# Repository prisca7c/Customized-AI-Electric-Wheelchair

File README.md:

# Customized-AI-Electric-Wheelchair

>PRISCA CHIEN | U0741Q95Y02
>
>July 27 2025
---

Manual wheelchair turned electric! This wheelchair uses electronic components such as modules and a PCB to make this wheelchair much for user interactive (and helps make life easier when you can't walk). 
I built this custom wheelchair because electric wheelchairs cost too much. Also it would be a great gift to my grandpa as he has Parkinson's disease. It has most of the functions on a regular wheelchair (motors, sound, speed, SOS, etc) AND I will be using AI as a healthcare tool in this project. 

---

## Full 3D Model of Wheelchair with Electronics (will not have those cuffs IRL 💀)

## PCB Schematic

## PCB Wiring Diagram (strapping 24V fan on just in case it does overheat), back copper pours for 24V, front copper pours for 12V I can't fit the wires if they're too large

## 3D View of PCB

---

# Bill of Materials (BOM)

| Reference | Qty | Description | Footprint | Purchase Link | Status |
|-----------|-----|-------------|-----------|---------------|---------|
| C1,C2,C3,C4,C6,C20,C23,C25 | 8 | Polarized Capacitor | CP_Radial_D5.0mm_P2.50mm | [AliExpress](https://www.aliexpress.com/item/1005002524973878.html) | |
| C5,C7,C8,C9,C10,C11,C12,C13,C14,C15,C16,C17,C18,C19,C22,C24 | 16 | Ceramic Capacitor | C_0603_1608Metric | [AliExpress](https://www.aliexpress.com/item/33000528620.html) | |
| C21 | 1 | Ceramic Capacitor (45°) | C_0603_1608Metric | [AliExpress](https://www.aliexpress.com/item/33000528620.html) | |
| D1 | 1 | TVS Diode | D_SMA | [AliExpress](https://www.aliexpress.com/item/1005002276080010.html) | |
| D2,D3,D4,D5,D8,D9,D10,D11,D12,D13,D14,D15,D16,D17,D18,D19 | 16 | Schottky Diode | D_SMA | [AliExpress](https://www.aliexpress.com/item/4001272645647.html) | |
| D6,D7 | 2 | LED | LED_D5.0mm | - | ✅ Have |
| F1 | 1 | Fuse | Fuse_BelFuse_0ZRE0005FF | - | ✅ Have |
| J1 | 1 | Buck Converter 24V→5V | PinSocket_1x04_P2.54mm | [AliExpress](https://www.aliexpress.com/item/1005006648976219.html) | |
| J2 | 1 | Buck Converter 24V→12V | FanPinHeader_1x04_P2.54mm | [AliExpress](https://www.aliexpress.com/item/1005004705881343.html) | |
| J3 | 1 | ICSP Programming Header | PinHeader_2x03_P2.54mm | - | ✅ Have |
| J4 | 1 | USB Serial | PinHeader_1x06_P1.00mm | - | ✅ Have |
| J5 | 1 | Raspberry Pi Zero | Harwin_M20-7812045_2x20 | [AliExpress](https://www.aliexpress.com/item/1005005792181612.html) | |
| J8 | 1 | Microphone | PinHeader_1x03_P1.00mm | [AliExpress](https://www.aliexpress.com/item/4001293896057.html) | |
| J9 | 1 | TFT 3.5" Display | PinHeader_1x14_P1.00mm | [AliExpress](https://www.aliexpress.com/item/1005008990800806.html) | |
| J10 | 1 | MPU6050 IMU | PinSocket_1x08_P2.54mm | [AliExpress](https://www.aliexpress.com/item/1005005682188615.html) | |
| J11 | 1 | DS3231 RTC | PinSocket_1x06_P2.54mm | [AliExpress](https://www.aliexpress.com/item/1005007143542894.html) | |
| J12 | 1 | Ultrasonic Sensor 1 | PinHeader_1x04_P1.00mm | - | ✅ Have |
| J13 | 1 | Ultrasonic Sensor 2 | PinHeader_1x04_P1.00mm | - | ✅ Have |
| J14 | 1 | Ultrasonic Sensor 3 | PinHeader_1x04_P1.00mm | - | ✅ Have |
| J15 | 1 | GPS Module | PinHeader_1x04_P1.00mm | [AliExpress](https://www.aliexpress.com/item/1005006459556070.html) | |
| J16 | 1 | Joystick Control | PinHeader_1x05_P1.00mm | - | ✅ Have |
| J17 | 1 | Temperature Sensor 1 | PinHeader_1x03_P1.00mm | - | ✅ Have |
| J18 | 1 | Temperature Sensor 2 | PinHeader_1x03_P1.00mm | - | ✅ Have |
| J19 | 1 | Servo 1 | PinHeader_1x02_P1.00mm | - | ✅ Have |
| J20 | 1 | Servo 2 | PinHeader_1x02_P1.00mm | - | ✅ Have |
| J21 | 1 | Linear Actuator | PinHeader_1x02_P1.00mm | - | ✅ Have |
| J22 | 1 | Audio Amplifier (LM386) | PinHeader_1x06_P1.00mm | [AliExpress](https://www.aliexpress.com/item/1005007577064258.html) | |
| J23 | 1 | Speaker | PinHeader_1x02_P1.00mm | [AliExpress](https://www.aliexpress.com/item/1005007504226811.html) | |
| J24 | 1 | XT60-M Power Connector | AMASS_XT60-M | [AliExpress](https://www.aliexpress.com/item/1005008955682135.html) | |
| J25,J26 | 2 | Motor Power Terminals | TerminalBlock_Phoenix_MKDS | [AliExpress](https://www.aliexpress.com/item/1005003179482974.html) | |
| Q1,Q2,Q3,Q4 | 4 | BSS138 MOSFET | SOT-23 | [AliExpress](https://www.aliexpress.com/item/1005009546772808.html) | |
| R1-R26 | 26 | Resistor | R_0603_1608Metric | - | ✅ Have |
| SW1 | 1 | SPST Switch | SW_PUSH-12mm | [AliExpress](https://www.aliexpress.com/item/1005006921918648.html) | |
| SW2-SW9 | 8 | Push Button | SW_PUSH-12mm | [AliExpress](https://www.aliexpress.com/item/1005007791349282.html) | |
| U1 | 1 | LM7805 Voltage Regulator | TO-220-3_Vertical | [AliExpress](https://www.aliexpress.com/item/10000200087213.html) | |
| U2 | 1 | AMS1117-3.3 Regulator | SOT-223-3_TabPin2 | [AliExpress](https://www.aliexpress.com/item/1005005774011848.html) | |
| U3 | 1 | ATMEGA2560-16AU MCU | TQFP100-0.5-14X14MM | [Digi-Key](https://www.digikey.ca/en/products/detail/microchip-technology/ATMEGA2560-16AU/735455) | |
| U4,U5,U6,U7 | 4 | BTS7960B Motor Driver | DPAK127P1490X440-8N | [AliExpress](https://www.aliexpress.com/item/1005006757604804.html) | |
| U9,U10 | 2 | L298N Motor Driver | TO-220-15_P2.54x2.54mm | [AliExpress](https://www.aliexpress.com/item/1462773567.html) | |
| U11 | 1 | ESP32-C3-MINI WiFi Module | XCVR_ESP32-C3-MINI-1-N4 | [AliExpress](https://www.aliexpress.com/item/1005007446928015.html) | |
| Y1 | 1 | Crystal Oscillator | Crystal_HC49-4H_Vertical | [AliExpress](https://www.aliexpress.com/item/1005002830871853.html) | |

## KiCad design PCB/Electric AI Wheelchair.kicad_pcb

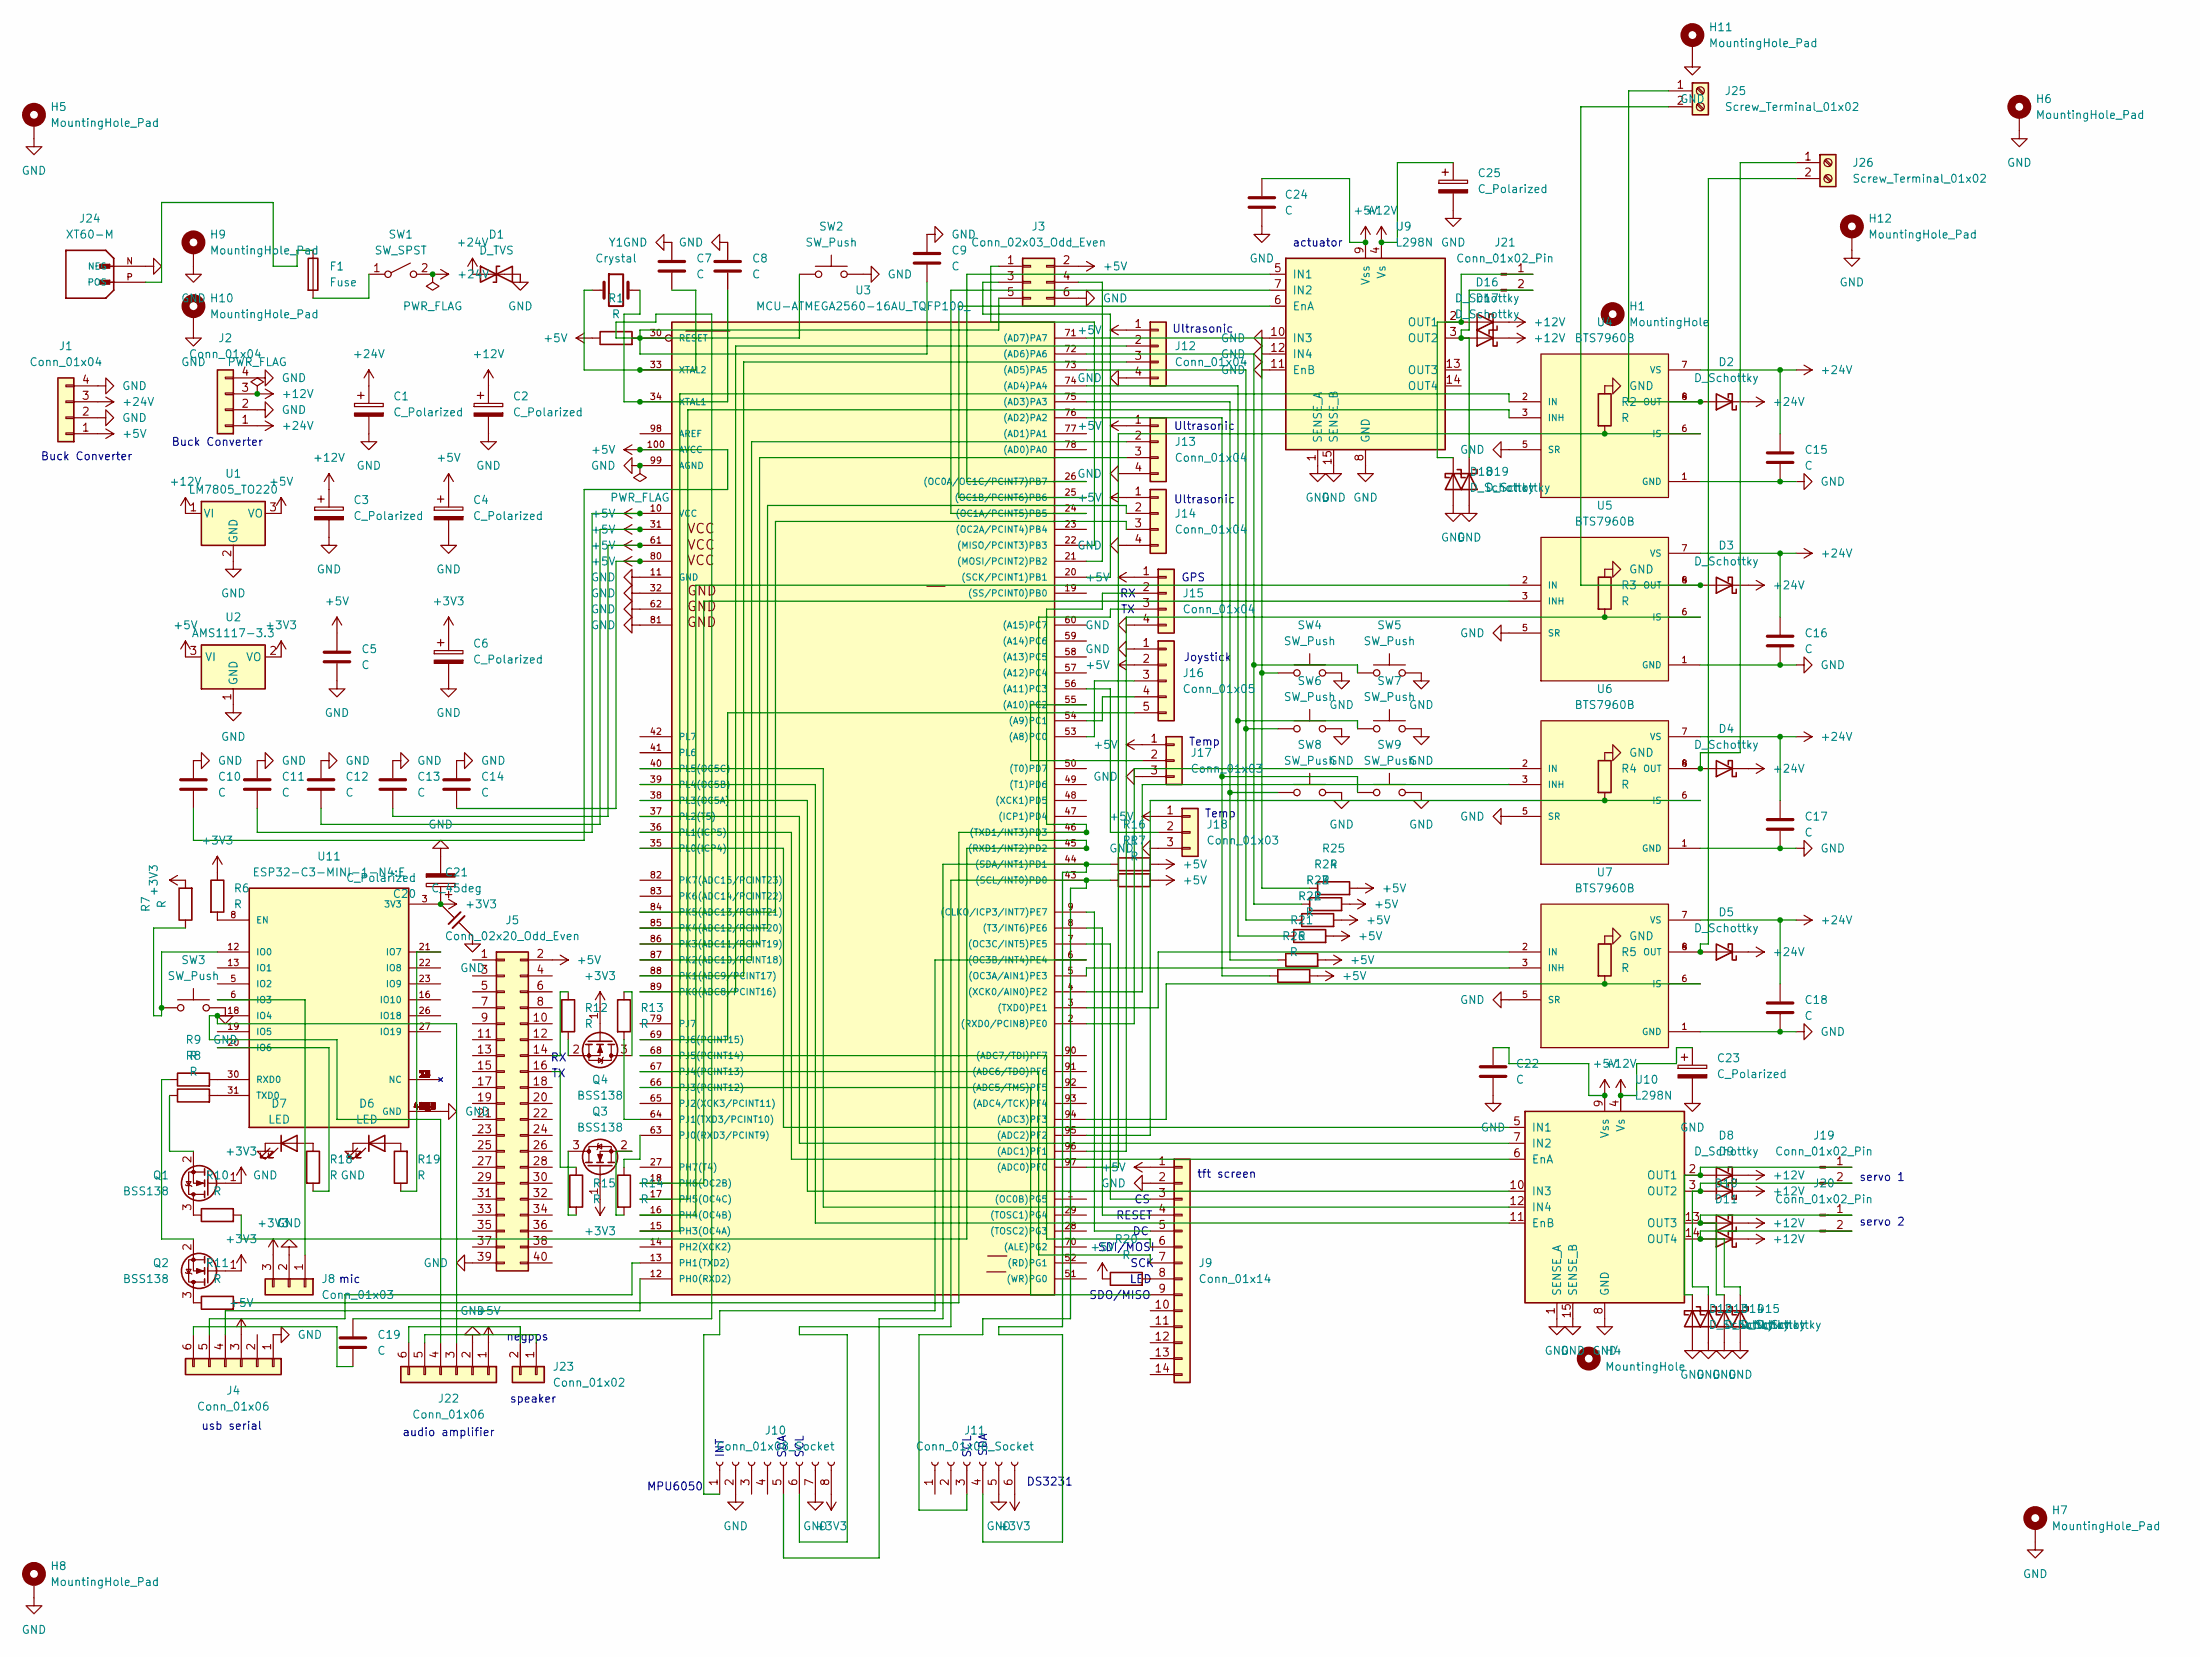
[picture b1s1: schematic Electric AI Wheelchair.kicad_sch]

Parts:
C1, C2, C3, C4, C6, C20, C23, C25: C_Polarized; CP_Radial_D5.0mm_P2.50mm
C5, C7, C8, C9, C10, C11, C12, C13, C14, C15, C16, C17, C18, C19, C22, C24: C; C_0603_1608Metric
C21: C_45deg; C_0603_1608Metric
D1: D_TVS; D_SMA
D2, D3, D4, D5, D8, D9, D10, D11, D12, D13, D14, D15, D16, D17, D18, D19: D_Schottky; D_SMA
D6, D7: LED; LED_D5.0mm
F1: Fuse; Fuse_BelFuse_0ZRE0005FF_L8.3mm_W3.8mm
H1, H4: MountingHole; MountingHole_2.7mm_M2.5
H5, H6, H7, H8: MountingHole_Pad; MountingHole_3.2mm_M3_Pad
H9, H10, H11, H12: MountingHole_Pad; MountingHole_3.2mm_M3_Pad_Via
J1: Conn_01x04; PinSocket_1x04_P2.54mm_Vertical_SMD_Pin1Left
J2: Conn_01x04; FanPinHeader_1x04_P2.54mm_Vertical
J3: Conn_02x03_Odd_Even; PinHeader_2x03_P2.54mm_Vertical
J4, J22: Conn_01x06; PinHeader_1x06_P1.00mm_Vertical_SMD_Pin1Left
J5: Conn_02x20_Odd_Even; Harwin_M20-7812045_2x20_P2.54mm_Vertical
J8, J17, J18: Conn_01x03; PinHeader_1x03_P1.00mm_Vertical_SMD_Pin1Left
J9: Conn_01x14; PinHeader_1x14_P1.00mm_Vertical_SMD_Pin1Left
J10: Conn_01x08_Socket; PinSocket_1x08_P2.54mm_Vertical_SMD_Pin1Left
J11: Conn_01x06_Socket; PinSocket_1x06_P2.54mm_Vertical_SMD_Pin1Left
J12, J13, J14, J15: Conn_01x04; PinHeader_1x04_P1.00mm_Vertical_SMD_Pin1Left
J16: Conn_01x05; PinHeader_1x05_P1.00mm_Vertical_SMD_Pin1Left
J19, J20, J21: Conn_01x02_Pin; PinHeader_1x02_P1.00mm_Vertical_SMD_Pin1Left
J23: Conn_01x02; PinHeader_1x02_P1.00mm_Vertical_SMD_Pin1Left
J24: XT60-M; AMASS_XT60-M; PARTREV V1.2
J25, J26: Screw_Terminal_01x02; TerminalBlock_Phoenix_MKDS-1,5-2_1x02_P5.00mm_Horizontal
Q1, Q2, Q3, Q4: BSS138; SOT-23
R1, R2, R3, R4, R5, R6, R7, R8, R9, R10, R11, R12, R13, R14, R15, R16, R17, R18, R19, R20, R21, R22, R23, R24, R25, R26: R; R_0603_1608Metric
SW1: SW_SPST; SW_PUSH-12mm
SW2, SW3, SW4, SW5, SW6, SW7, SW8, SW9: SW_Push; SW_PUSH-12mm
U1: LM7805_TO220; TO-220-3_Vertical
U2: AMS1117-3.3; SOT-223-3_TabPin2
U3: MCU-ATMEGA2560-16AU_TQFP100_; TQFP100-0.5-14X14MM; MPN ATMEGA2560-16AU
U4, U5, U6, U7: BTS7960B; DPAK127P1490X440-8N; PARTREV 1.1
U9, U10: L298N; TO-220-15_P2.54x2.54mm_StaggerOdd_Lead5.84mm_TabDown
U11: ESP32-C3-MINI-1-N4:E; XCVR_ESP32-C3-MINI-1-N4; PARTREV v1.0
Y1: Crystal; Crystal_HC49-4H_Vertical

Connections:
+3V3: C6.1, C20.1, C21.2, J8.3, J10.8, J11.6, Q1.1 (G), Q2.1 (G), Q3.1 (G), Q4.1 (G), R6.1, R7.2, U2.2 (VO), U11.3 (3V3)
+5V: C4.1, C5.1, C10.2, C11.2, C12.2, C13.2, C14.2, C22.1, C24.1, J1.1, J3.2, J4.3, J5.2, J9.1, J12.1, J13.1, J14.1, J15.1, J16.2, J17.1, J18.1, J22.1, R1.1, R16.2, R17.2, R20.1, R21.2, R22.2, R23.2, R24.2, R25.2, R26.2, U1.3 (VO), U2.3 (VI), U3.10 (VCC), U3.31, U3.61, U3.80, U3.100 (AVCC), U9.9 (Vss), U10.9 (Vss)
+12V: C2.1, C3.1, C23.1, C25.1, D8.1 (K), D9.1 (K), D10.1 (K), D11.1 (K), D16.1 (K), D17.1 (K), J2.3, U1.1 (VI), U9.4 (Vs), U10.4 (Vs)
+24V: C1.1, C15.1, C16.1, C17.1, C18.1, D1.1 (A1), D2.1 (K), D3.1 (K), D4.1 (K), D5.1 (K), J1.3, J2.1, SW1.2 (B), U4.7 (VS), U5.7 (VS), U6.7 (VS), U7.7 (VS)
GND: C1.2, C2.2, C3.2, C4.2, C5.2, C6.2, C7.1, C8.1, C9.1, C10.1, C11.1, C12.1, C13.1, C14.1, C15.2, C16.2, C17.2, C18.2, C20.2, C21.1, C22.2, C23.2, C24.2, C25.2, D1.2 (A2), D6.1 (K), D7.1 (K), D12.2 (A), D13.2 (A), D14.2 (A), D15.2 (A), D18.2 (A), D19.2 (A), H5.1, H6.1, H7.1, H8.1, H9.1, H10.1, H11.1, H12.1, J1.2, J1.4, J2.2, J2.4, J3.6, J4.1, J5.39, J8.2, J9.2, J10.2, J10.7, J11.5, J12.4, J13.4, J14.4, J15.4, J16.1, J17.3, J18.3, J22.2, J24.N (NEG), R2.1, R3.1, R4.1, R5.1, SW2.2, SW3.2, SW4.2, SW5.2, SW6.2, SW7.2, SW8.2, SW9.2, U1.2 (GND), U2.1 (GND), U3.11 (GND), U3.32, U3.62, U3.81, U3.99 (AGND), U4.1 (GND), U4.5 (SR), U5.1 (GND), U5.5 (SR), U6.1 (GND), U6.5 (SR), U7.1 (GND), U7.5 (SR), U9.1 (SENSE_A), U9.8 (GND), U9.10 (IN3), U9.11 (EnB), U9.12 (IN4), U9.15 (SENSE_B), U10.1 (SENSE_A), U10.8 (GND), U10.15 (SENSE_B), U11.1 (GND), U11.2 (GND), U11.11 (GND), U11.14 (GND), U11.36 (GND), U11.37 (GND), U11.38 (GND), U11.39 (GND), U11.40 (GND), U11.41 (GND), U11.42 (GND), U11.43 (GND), U11.44 (GND), U11.45 (GND), U11.46 (GND), U11.47 (GND), U11.48 (GND), U11.49_1 (GND), U11.49_2 (GND), U11.49_3 (GND), U11.49_4 (GND), U11.49_5 (GND), U11.49_6 (GND), U11.49_7 (GND), U11.49_8 (GND), U11.49_9 (GND), U11.50 (GND), U11.51 (GND), U11.52 (GND), U11.53 (GND)
unnamed: D2.2 (A), J25.1, U4.4 (OUT), U4.8 (OUT)
unnamed: D3.2 (A), J25.2, U5.4 (OUT), U5.8 (OUT)
unnamed: D4.2 (A), J26.1, U6.4 (OUT), U6.8 (OUT)
unnamed: D5.2 (A), J26.2, U7.4 (OUT), U7.8 (OUT)
unnamed: D6.2 (A), R19.2
unnamed: D7.2 (A), R18.1
unnamed: D10.2 (A), D14.1 (K), J20.1, U10.13 (OUT3)
unnamed: D11.2 (A), D15.1 (K), J20.2, U10.14 (OUT4)
unnamed: D8.2 (A), D12.1 (K), J19.1, U10.2 (OUT1)
unnamed: D9.2 (A), D13.1 (K), J19.2, U10.3 (OUT2)
unnamed: D16.2 (A), D18.1 (K), J21.1, U9.2 (OUT1)
unnamed: D17.2 (A), D19.1 (K), J21.2, U9.3 (OUT2)
unnamed: J3.1, U3.22 ((MISO/PCINT3)PB3)
unnamed: J3.3, U3.20 ((SCK/PCINT1)PB1)
unnamed: J3.4, U3.21 ((MOSI/PCINT2)PB2)
unnamed: C9.2, C19.1, J3.5, R1.2, SW2.1, U3.30 (RESET)
unnamed: J4.4, U3.12 (PH0(RXD2))
unnamed: J4.5, U3.13 (PH1(TXD2))
unnamed: C19.2, J4.6
unnamed: J5.14, R12.1
unnamed: J5.16, R15.1
unnamed: J8.1, U11.6 (IO3)
unnamed: J9.3, U3.7 ((OC3C/INT5)PE5)
unnamed: J9.4, U3.8 ((T3/INT6)PE6)
unnamed: J9.5, U3.9 ((CLKO/ICP3/INT7)PE7)
unnamed: J9.6, U3.68 (PJ5(PCINT14))
unnamed: J9.7, U3.67 (PJ4(PCINT13))
unnamed: J9.8, R20.2
unnamed: J9.9, U3.66 (PJ3(PCINT12))
unnamed: J10.1, U3.6 ((OC3B/INT4)PE4)
unnamed: J10.5, J11.4, R16.1, U3.44 ((SDA/INT1)PD1)
unnamed: J10.6, J11.3, R17.1, U3.43 ((SCL/INT0)PD0)
unnamed: J12.2, U3.89 (PK0(ADC8/PCINT16))
unnamed: J12.3, U3.88 (PK1(ADC9/PCINT17))
unnamed: J13.2, U3.87 (PK2(ADC10/PCINT18))
unnamed: J13.3, U3.86 (PK3(ADC11/PCINT19))
unnamed: J14.2, U3.85 (PK4(ADC12/PCINT20))
unnamed: J14.3, U3.84 (PK5(ADC13/PCINT21))
unnamed: J15.2, R11.2, U3.46 ((TXD1/INT3)PD3)
unnamed: J15.3, R10.2, U3.45 ((RXD1/INT2)PD2)
unnamed: J16.3, U3.53 ((A8)PC0)
unnamed: J16.4, U3.54 ((A9)PC1)
unnamed: J16.5, U3.69 (PJ6(PCINT15))
unnamed: J17.2, U3.55 ((A10)PC2)
unnamed: J18.2, U3.56 ((A11)PC3)
unnamed: J22.3, J22.4, U11.18 (IO4)
unnamed: J22.5, J23.1
unnamed: J22.6, J23.2
unnamed: F1.1, J24.P (POS)
unnamed: Q1.3 (D), R10.1
unnamed: Q1.2 (S), R8.1
unnamed: Q2.3 (D), R11.1
unnamed: Q2.2 (S), R9.1
unnamed: Q3.3 (D), R15.2
unnamed: Q3.2 (S), R14.2
unnamed: Q4.3 (D), R13.1
unnamed: Q4.2 (S), R12.2
unnamed: F1.2, SW1.1 (A)
unnamed: R26.1, SW9.1, U3.76 ((AD2)PA2)
unnamed: R21.1, SW8.1, U3.75 ((AD3)PA3)
unnamed: R22.1, SW7.1, U3.74 ((AD4)PA4)
unnamed: R23.1, SW6.1, U3.73 ((AD5)PA5)
unnamed: R24.1, SW5.1, U3.72 ((AD6)PA6)
unnamed: R25.1, SW4.1, U3.71 ((AD7)PA7)
unnamed: R2.2, U3.97 ((ADC0)PF0), U4.6 (IS)
unnamed: R3.2, U3.96 ((ADC1)PF1), U5.6 (IS)
unnamed: R4.2, U3.95 ((ADC2)PF2), U6.6 (IS)
unnamed: R5.2, U3.94 ((ADC3)PF3), U7.6 (IS)
unnamed: U3.26 ((OC0A/OC1C/PCINT7)PB7), U9.5 (IN1)
unnamed: U3.24 ((OC1A/PCINT5)PB5), U9.7 (IN2)
unnamed: U3.25 ((OC1B/PCINT6)PB6), U9.6 (EnA)
unnamed: U3.5 ((OC3A/AIN1)PE3), U7.3 (INH)
unnamed: U3.2 ((RXD0/PCIN8)PE0), U6.2 (IN)
unnamed: U3.3 ((TXD0)PE1), U7.2 (IN)
unnamed: U3.4 ((XCK0/AIN0)PE2), U6.3 (INH)
unnamed: U3.15 (PH3(OC4A)), U4.2 (IN)
unnamed: U3.16 (PH4(OC4B)), U5.2 (IN)
unnamed: U3.17 (PH5(OC4C)), U4.3 (INH)
unnamed: U3.18 (PH6(OC2B)), U5.3 (INH)
unnamed: R14.1, U3.63 (PJ0(RXD3/PCINT9))
unnamed: R13.2, U3.64 (PJ1(TXD3/PCINT10))
unnamed: C8.2, U3.34 (XTAL1), Y1.2
unnamed: C7.2, U3.33 (XTAL2), Y1.1
unnamed: U3.36 (PL1(ICP5)), U10.6 (EnA)
unnamed: U3.39 (PL4(OC5B)), U10.11 (EnB)
unnamed: U3.35 (PL0(ICP4)), U10.5 (IN1)
unnamed: U3.37 (PL2(T5)), U10.7 (IN2)
unnamed: U3.38 (PL3(OC5A)), U10.10 (IN3)
unnamed: U3.40 (PL5(OC5C)), U10.12 (IN4)
unnamed: R6.2, U11.8 (EN)
unnamed: R7.1, SW3.1, U11.12 (IO0)
unnamed: R18.2, U11.20 (IO6)
unnamed: R19.1, U11.21 (IO7)
unnamed: R9.2, U11.30 (RXD0)
unnamed: R8.2, U11.31 (TXD0)

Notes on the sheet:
SCL
Buck Converter
servo 2
SCK
speaker
Temp
SDO/MISO
audio amplifier
Ultrasonic
LED
mic
SDI/MOSI
SDA
servo 1
INT
usb serial
GPS
Joystick
tft screen
RESET
MPU6050
actuator
neg
DS3231
pos

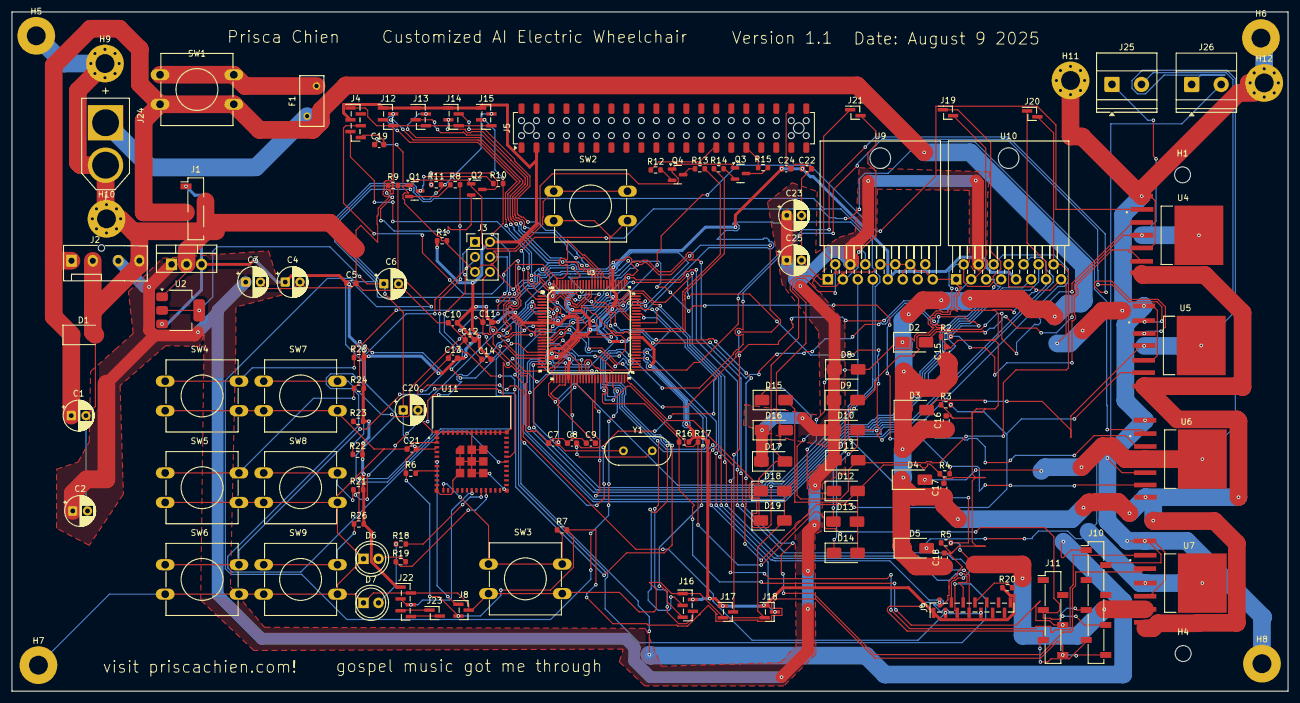
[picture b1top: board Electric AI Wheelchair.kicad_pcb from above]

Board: 2 copper layers, 216.3 x 115.1 mm, 129 parts (0 on the bottom side), 100 nets.

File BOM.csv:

Reference,Qty,Value,DNP,Exclude from BOM,Exclude from Board,Footprint,Datasheet
"C1,C2,C3,C4,C6,C20,C23,C25",8,C_Polarized,,,,"Capacitor_THT:CP_Radial_D5.0mm_P2.50mm",https://www.aliexpress.com/item/1005002524973878.html
"C5,C7,C8,C9,C10,C11,C12,C13,C14,C15,C16,C17,C18,C19,C22,C24",16,C,,,,"Capacitor_SMD:C_0603_1608Metric",https://www.aliexpress.com/item/33000528620.html
C21,1,C_45deg,,,,"Capacitor_SMD:C_0603_1608Metric",https://www.aliexpress.com/item/33000528620.html
D1,1,D_TVS,,,,"Diode_SMD:D_SMA",https://www.aliexpress.com/item/1005002276080010.html
"D2,D3,D4,D5,D8,D9,D10,D11,D12,D13,D14,D15,D16,D17,D18,D19",16,D_Schottky,,,,"Diode_SMD:D_SMA",https://www.aliexpress.com/item/4001272645647.html
"D6,D7",2,LED,,,,"LED_THT:LED_D5.0mm",~already have
F1,1,Fuse,,,,"Fuse:Fuse_BelFuse_0ZRE0005FF_L8.3mm_W3.8mm",~already have
"H1,H4",2,MountingHole,,Excluded from BOM,,"MountingHole:MountingHole_2.7mm_M2.5",~
"H5,H6,H7,H8",4,MountingHole_Pad,,Excluded from BOM,,"MountingHole:MountingHole_3.2mm_M3_Pad",~
"H9,H10,H11,H12",4,MountingHole_Pad,,Excluded from BOM,,"MountingHole:MountingHole_3.2mm_M3_Pad_Via",~
J1,1,Buck_Converter_24V-5V,,,,"Connector_PinSocket_2.54mm:PinSocket_1x04_P2.54mm_Vertical_SMD_Pin1Left",https://www.aliexpress.com/item/1005006648976219.html
J2,1,Buck_Converter_24V-12V,,,,"Connector:FanPinHeader_1x04_P2.54mm_Vertical",https://www.aliexpress.com/item/1005004705881343.html
J3,1,ICSP_Programming_Header,,,,"Connector_PinHeader_2.54mm:PinHeader_2x03_P2.54mm_Vertical",~already have
J4,1,USB_Serial,,,,"Connector_PinHeader_1.00mm:PinHeader_1x06_P1.00mm_Vertical_SMD_Pin1Left",~already have
J5,1,Raspberry_Pi_Zero,,,,"Connector_Harwin:Harwin_M20-7812045_2x20_P2.54mm_Vertical",https://www.aliexpress.com/item/1005005792181612.html
J8,1,Microphone,,,,"Connector_PinHeader_1.00mm:PinHeader_1x03_P1.00mm_Vertical_SMD_Pin1Left",https://www.aliexpress.com/item/4001293896057.html
J9,1,TFT_3.5_Display,,,,"Connector_PinHeader_1.00mm:PinHeader_1x14_P1.00mm_Vertical_SMD_Pin1Left",https://www.aliexpress.com/item/1005008990800806.html
J10,1,MPU6050_IMU,,,,"Connector_PinSocket_2.54mm:PinSocket_1x08_P2.54mm_Vertical_SMD_Pin1Left",https://www.aliexpress.com/item/1005005682188615.html
J11,1,DS3231_RTC,,,,"Connector_PinSocket_2.54mm:PinSocket_1x06_P2.54mm_Vertical_SMD_Pin1Left",https://www.aliexpress.com/item/1005007143542894.html
J12,1,Ultrasonic_Sensor_1,,,,"Connector_PinHeader_1.00mm:PinHeader_1x04_P1.00mm_Vertical_SMD_Pin1Left",~already have
J13,1,Ultrasonic_Sensor_2,,,,"Connector_PinHeader_1.00mm:PinHeader_1x04_P1.00mm_Vertical_SMD_Pin1Left",~already have
J14,1,Ultrasonic_Sensor_3,,,,"Connector_PinHeader_1.00mm:PinHeader_1x04_P1.00mm_Vertical_SMD_Pin1Left",~already have
J15,1,GPS_Module,,,,"Connector_PinHeader_1.00mm:PinHeader_1x04_P1.00mm_Vertical_SMD_Pin1Left",https://www.aliexpress.com/item/1005006459556070.html
J16,1,Joystick_Control,,,,"Connector_PinHeader_1.00mm:PinHeader_1x05_P1.00mm_Vertical_SMD_Pin1Left",~already have
J17,1,Temperature_Sensor_1,,,,"Connector_PinHeader_1.00mm:PinHeader_1x03_P1.00mm_Vertical_SMD_Pin1Left",~already have
J18,1,Temperature_Sensor_2,,,,"Connector_PinHeader_1.00mm:PinHeader_1x03_P1.00mm_Vertical_SMD_Pin1Left",~already have
J19,1,Servo_1,,,,"Connector_PinHeader_1.00mm:PinHeader_1x02_P1.00mm_Vertical_SMD_Pin1Left",~already have
J20,1,Servo_2,,,,"Connector_PinHeader_1.00mm:PinHeader_1x02_P1.00mm_Vertical_SMD_Pin1Left",~already have
J21,1,Linear_Actuator,,,,"Connector_PinHeader_1.00mm:PinHeader_1x02_P1.00mm_Vertical_SMD_Pin1Left",~already have
J22,1,Audio_Amplifier,,,,"Connector_PinHeader_1.00mm:PinHeader_1x06_P1.00mm_Vertical_SMD_Pin1Left",https://www.aliexpress.com/item/1005007577064258.html
J23,1,Speaker,,,,"Connector_PinHeader_1.00mm:PinHeader_1x02_P1.00mm_Vertical_SMD_Pin1Left",https://www.aliexpress.com/item/1005007504226811.html
J24,1,XT60-M,,,,"XT60-M:AMASS_XT60-M",https://www.aliexpress.com/item/1005008955682135.html
"J25,J26",2,Motor_1_Motor_2_Power,,,,"TerminalBlock_Phoenix:TerminalBlock_Phoenix_MKDS-1,5-2_1x02_P5.00mm_Horizontal",https://www.aliexpress.com/item/1005003179482974.html
"Q1,Q2,Q3,Q4",4,BSS138,,,,"Package_TO_SOT_SMD:SOT-23",https://www.aliexpress.com/item/1005009546772808.html
"R1,R2,R3,R4,R5,R6,R7,R8,R9,R10,R11,R12,R13,R14,R15,R16,R17,R18,R19,R20,R21,R22,R23,R24,R25,R26",26,R,,,,"Resistor_SMD:R_0603_1608Metric",~already have
SW1,1,SW_SPST,,,,"Button_Switch_THT:SW_PUSH-12mm",https://www.aliexpress.com/item/1005006921918648.html
"SW2,SW3,SW4,SW5,SW6,SW7,SW8,SW9",8,SW_Push,,,,"Button_Switch_THT:SW_PUSH-12mm",https://www.aliexpress.com/item/1005007791349282.html
U1,1,LM7805_TO220,,,,"Package_TO_SOT_THT:TO-220-3_Vertical",https://www.aliexpress.com/item/10000200087213.html
U2,1,AMS1117-3.3,,,,"Package_TO_SOT_SMD:SOT-223-3_TabPin2",https://www.aliexpress.com/item/1005005774011848.html
U3,1,MCU-ATMEGA2560-16AU_TQFP100_,,,,"MCU-ATMEGA2560-16AU_TQFP100_:TQFP100-0.5-14X14MM",https://www.digikey.ca/en/products/detail/microchip-technolo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
"U4,U5,U6,U7",4,BTS7960B,,,,"BTS7960B:DPAK127P1490X440-8N",https://www.aliexpress.com/item/1005006757604804.html
"U9,U10",2,L298N,,,,"Package_TO_SOT_THT:TO-220-15_P2.54x2.54mm_StaggerOdd_Lead5.84mm_TabDown",https://www.aliexpress.com/item/1462773567.html
U11,1,ESP32-C3-MINI-1-N4:E,,,,"ESP32-C3-MINI-1-N4:XCVR_ESP32-C3-MINI-1-N4",https://www.aliexpress.com/item/1005007446928015.html?spm=a2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
Y1,1,Crystal,,,,"Crystal:Crystal_HC49-4H_Vertical",https://www.aliexpress.com/item/1005002830871853.html

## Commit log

2025-07-31 Create ya
2025-07-31 Create PCB
2025-08-01 Rename bom.csv to BOM.csv
